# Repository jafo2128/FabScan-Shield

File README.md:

# FabScan-Shield
The FabScan-Shield is a plug-on module for Arduino/Genuino to drive Stepper and Servo Motors or to build a 3D Laser Scanner.

Infos about the FabScan 3D-Scanner: http://hci.rwth-aachen.de/fabscan

## Shop
* [FabScan-Shield](http://www.watterott.com/en/Arduino-FabScan-Shield)
* [FabScan Cube Kit with USB camera](http://www.watterott.com/en/FabScan-Cube-complete-Kit)
* [FabScan Cube Kit without USB camera](http://www.watterott.com/en/FabScan-Cube-Electronics)
* [FabScan Cube Wood Parts](http://www.watterott.com/en/Fabscan-CUBE-Kit)
* [FabScan Cube Screw Set](http://www.watterott.com/en/FabScan-Cube-Screw-set)

## Features
* Drive up to 3 (v1.0) or 4 (v1.1) stepper motors (requires Pololu A4988 or StepStick) or servo motors
* Compatible with FabScan (3D Laser Scanner)

## Hardware and Software
* [Schematics + Layout](https://github.com/watterott/FabScan-Shield/tree/master/hardware)
* [Arduino Examples](https://github.com/watterott/FabScan-Shield/tree/master/software)
* FabScan: [Shield Assembly Instructions](http://hci.rwth-aachen.de/fabscan_shield), [Assembly Instructions](http://32b.it/assembly-fabscan-by-wetterott-my-personal-instruction-guide/), [Scanning Instructions](http://www.mariolukas.de/2014/07/scannen-mit-dem-fabscan/)

Finally words from us Archivers and Developers.. 

##### Donate

People from time to time wish to donate a little money. Donating won't get you anything special, other than a warm feeling inside, and possibly urge me to produce more freely available material for interesting projects. You can donate via [PayPal](https://www.paypal.com), just click [donate](https://www.paypal.com/cgi-bin/webscr?cmd=_s-xclick&hosted_button_id=3PXVSLXFBS45E) button available below - it will redirect you to the secured PayPal page where you can provide donation amount (there is no minimal value). Any donations are apreciated greatly, and we thank you all in advance for your support along the ways..

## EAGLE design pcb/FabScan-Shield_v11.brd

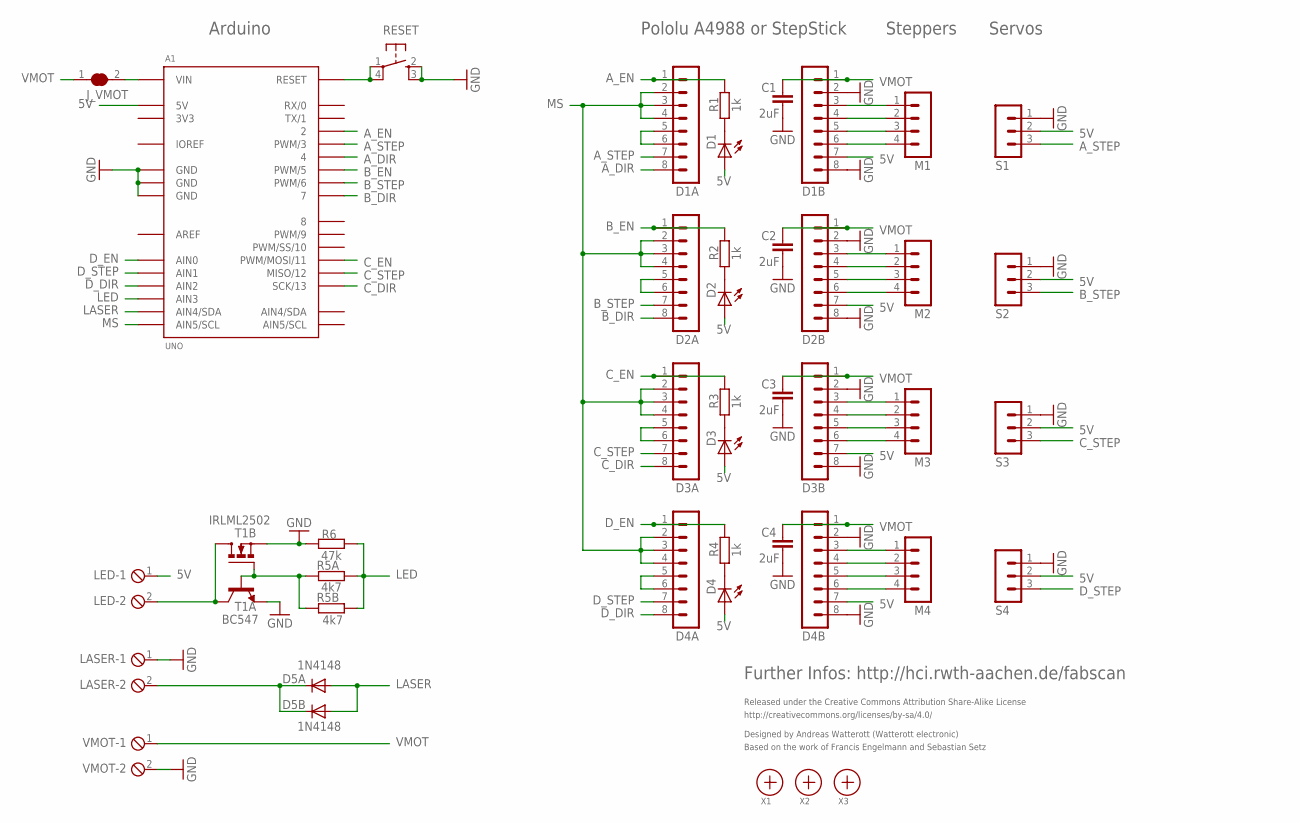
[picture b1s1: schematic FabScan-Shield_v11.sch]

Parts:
A1: UNO
C1, C2, C3, C4: 2uF; C0603
D1, D2, D3, D4: LEDCHIPLED_0603; CHIPLED_0603
D1A, D1B, D2A, D2B, D3A, D3B, D4A, D4B: MA08-1
D5A: 1N4148; DO35-7
D5B: 1N4148; SOD106-R
J_VMOT: SJ
LASER: MPT2; 2POL254
LED: MPT2; 2POL254
M1, M2, M3, M4: MA04-1
R1, R2, R3, R4: 1k; R0603
R5A: 4k7; 0204/7
R5B: 4k7; R0603
R6: 47k; R0603
RESET: SW_SMDS; SW_SMD4
S1, S2, S3, S4: MA03-1
T1A: BC547; TO92
T1B: IRLML2502; MICRO3
VMOT: MPT2; 2POL254
X1, X2, X3: PASSER

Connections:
3V3: A1.3V3
5V: A1.5V, D1.A, D1B.7, D2.A, D2B.7, D3.A, D3B.7, D4.A, D4B.7, LED.1, S1.2, S2.2, S3.2, S4.2
AREF: A1.AREF
A_1A: D1B.5, M1.3
A_1B: D1B.6, M1.4
A_2A: D1B.4, M1.2
A_2B: D1B.3, M1.1
A_DIR: A1.4, D1A.8
A_EN: A1.2, D1A.1, R1.1
A_RST: D1A.5, D1A.6
A_STEP: A1.3 (PWM/3), D1A.7, S1.3
B_1A: D2B.5, M2.3
B_1B: D2B.6, M2.4
B_2A: D2B.4, M2.2
B_2B: D2B.3, M2.1
B_DIR: A1.7, D2A.8
B_EN: A1.5 (PWM/5), D2A.1, R2.1
B_STEP: A1.6 (PWM/6), D2A.7, S2.3
C_1A: D3B.5, M3.3
C_1B: D3B.6, M3.4
C_2A: D3B.4, M3.2
C_2B: D3B.3, M3.1
C_DIR: A1.13 (SCK/13), D3A.8
C_EN: A1.11 (PWM/MOSI/11), D3A.1, R3.1
C_STEP: A1.12 (MISO/12), D3A.7, S3.3
D_1A: D4B.5, M4.3
D_1B: D4B.6, M4.4
D_2A: D4B.4, M4.2
D_2B: D4B.3, M4.1
D_DIR: A1.AIN2, D4A.8
D_EN: A1.AIN0, D4A.1, R4.1
D_STEP: A1.AIN1, D4A.7, S4.3
GND: A1.GND@1 (GND), A1.GND@2 (GND), A1.GND@3 (GND), C1.2, C2.2, C3.2, C4.2, D1B.2, D1B.8, D2B.2, D2B.8, D3B.2, D3B.8, D4B.2, D4B.8, LASER.1, R6.2, RESET.2 (S), RESET.3 (S1), S1.1, S2.1, S3.1, S4.1, T1A.1 (E), T1B.2 (S), VMOT.2
IOREF: A1.IOREF
LASER: A1.AIN4 (AIN4/SDA), D5A.A, D5B.A
LED: A1.AIN3, R5A.1, R5B.2, R6.1
MS: A1.AIN5 (AIN5/SCL), D1A.2, D1A.3, D1A.4, D2A.2, D2A.3, D2A.4, D3A.2, D3A.3, D3A.4, D4A.2, D4A.3, D4A.4
unnamed: D5A.C, D5B.C, LASER.2
unnamed: D1.C, R1.2
unnamed: D2.C, R2.2
unnamed: D3.C, R3.2
unnamed: D4A.5, D4A.6
unnamed: LED.2, T1A.3 (C), T1B.3 (D)
unnamed: D4.C, R4.2
unnamed: R5A.2, R5B.1, T1A.2 (B), T1B.1 (G)
unnamed: D2A.5, D2A.6
unnamed: D3A.5, D3A.6
RST: A1.RST (RESET), RESET.1, RESET.4 (P1)
VIN: A1.VIN, J_VMOT.2
VMOT: C1.1, C2.1, C3.1, C4.1, D1B.1, D2B.1, D3B.1, D4B.1, J_VMOT.1, VMOT.1

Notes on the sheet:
Released under the Creative Commons Attribution Share-Alike License
http://creativecommons.org/licenses/by-sa/4.0/
Designed by Andreas Watterott (Watterott electronic)
Further Infos: http://hci.rwth-aachen.de/fabscan
Based on the work of Francis Engelmann and Sebastian Setz
Servos
Steppers
Arduino
Pololu A4988 or StepStick

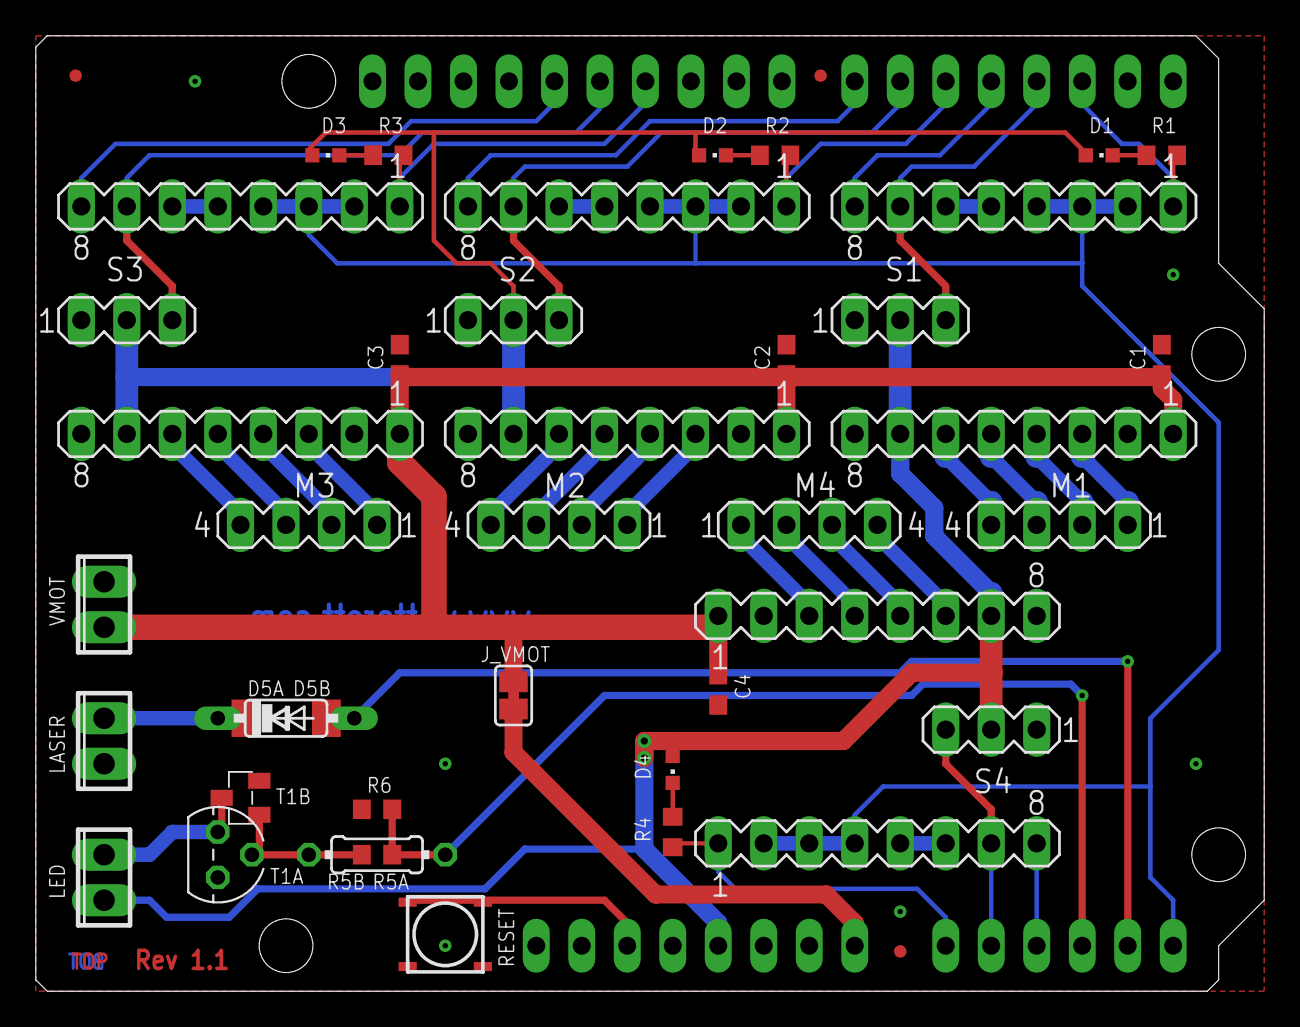
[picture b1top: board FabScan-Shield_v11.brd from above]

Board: 2 copper layers, 68.6 x 53.3 mm, 44 parts (0 on the bottom side), 47 nets.

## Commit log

2012-11-26 added schematic and layout files
2012-12-07 upated schematics
2013-01-16 added Arduino examples
2013-01-17 updated readme added image
2013-03-11 added project list
2013-03-26 added assembly infos updated readme + projects
2013-08-18 added pcb v1.1
2013-08-19 updated image
2014-08-15 updated projects
2014-08-15 updated schematic and layout files
2014-08-21 updated layout and schematics
2014-09-18 removed beta layout
2014-10-24 added assembly guide
2014-11-06 cleaned up schematics and layout
2015-01-10 moved image
2015-05-23 updated schematics
2015-08-21 changed path structure
